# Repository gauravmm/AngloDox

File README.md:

# AngloDox Keyboard

This is yet another split keyboard with the following features:

- Per-key RGB LEDs
- Separate function row
- RC-circuit debouncing for each key (the internal pullups allow you to swap switches while the keyboard is on!)
- Kailh hot-swap sockets
- USB-C connectors (but I2C protocol!) for the halves, with ESD protection
- Key polling via shift register instead of matrix
- Entirely manufacturable by JLCPCB, using basic parts as much as possible.

### Keyboard Layout

The keyboard layout is specified in `keyboard-layout.json` and can be edited in [KLE](http://www.keyboard-layout-editor.com/). The current layout is based on the reference ANSI-104 layout, with a macro column on the left, a collapsed arrow cluster on the right, and added thumb clusters from the venerable Ergodox keyboard.

The current layout has 46 keys on the left and 54 on the right, for a total of 100 keys.

## Development

This relies on a combination of scripts and hand-routing. Here's the general workflow:

    1. Generate the basic circuitry as a hierarchical schematic in KiCad.
    2. Specify a key layout as a [http://www.keyboard-layout-editor.com/#/](KLE) JSON file.
    3. Run the [KLE Placement Plugin](TODO) for the key layout.
    4. Specify the layout for each key next to the schematic for the key.
    5. Enforce the layout using the [HierarchicalPCB plugin](https://github.com/gauravmm/HierarchicalPcb).
    6. Route the parts between keys, using the swap positions option in the KLE Placement Plugin to improve performance.

### Regenerate KiCad Library

The Kicad library is generated using [JLC2KiCad_lib](https://github.com/TousstNicolas/JLC2KiCad_lib). To regenerate the library, run:

```bash
JLC2KiCadLib C1525 C25779 C36871 C965555 \
    -dir temp_jlc_import/
```

Then merge the symbol and footprint libraries into the main library manually. Remember to update the Value field of the symbols.

When setting up the Footprint library, set the nickname to `footprint`.

### Design Notes

Component selection is driven by what is available on JLCPCB as a basic part, making construction as cheap as possible. The only extended parts are the USB ESD protection circuit and the RJ11 connectors.

#### Crystal Design

We choose a [generic 12MHz oscillator](https://jlcpcb.com/partdetail/YangxingTech-X322512MSB4SI/C9002) as it is the cheapest basic part available on LCSC. As the load capacitance is 20pF, and the stray capacitance is assumed to be 5pF, we need a pair of 30pF capacitors to get the right frequency. (See [section 3.3 of the application note](https://www.st.com/resource/en/application_note/cd00221665-oscillator-design-guide-for-stm8af-al-s-stm32-mcus-and-mpus-stmicroelectronics.pdf) for the derivation.)

#### ESD Protection

For peace of mind, we add ESD protection to both USB-C ports.

1. Use a [generic bi-directional 6V TVS diode](https://jlcpcb.com/partdetail/Liown-SMF60CA/C2990473) between `VBUS` and `GND`.
2. Use a [USB-specific ESD protection circuit](https://jlcpcb.com/partdetail/Stmicroelectronics-USBLC62SC6/C7519) on the data lines. This is one of the few extended parts we use. This is based on the suggestions in [Phil's Lab tutorial](https://youtu.be/C7-8nUU6e3E?t=3842).
3. Short shield pins to GND directly. (This disagrees with the tutorial mentioned above.)

#### Half-to-half Connection

The halves are connected via USB-C to USB-C cables. This is preferable to TRRS cables (which have a nasty habit of shorting connections) and RJ11 cables (which are painfully tall and would have to be hand-soldered later). Since we're already paying the extended part fee for the connector, we might as well use them and enjoy the reversible connection it grants us.

To prevent damage from accidental connections, we apply the same ESD protections to the half-to-half connections as we do to the legitimate USB-C port.

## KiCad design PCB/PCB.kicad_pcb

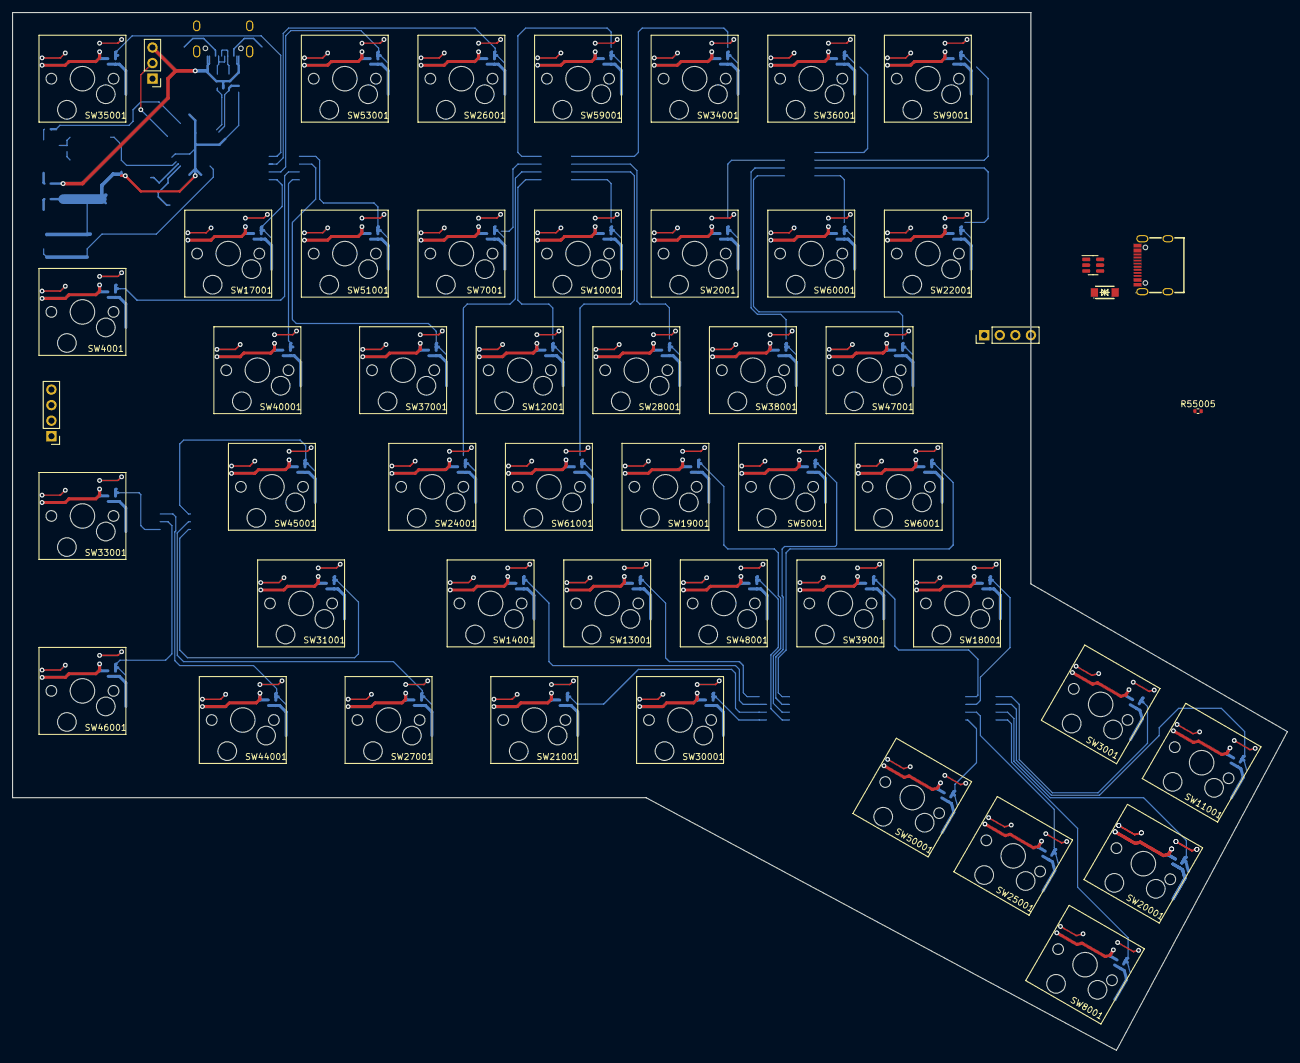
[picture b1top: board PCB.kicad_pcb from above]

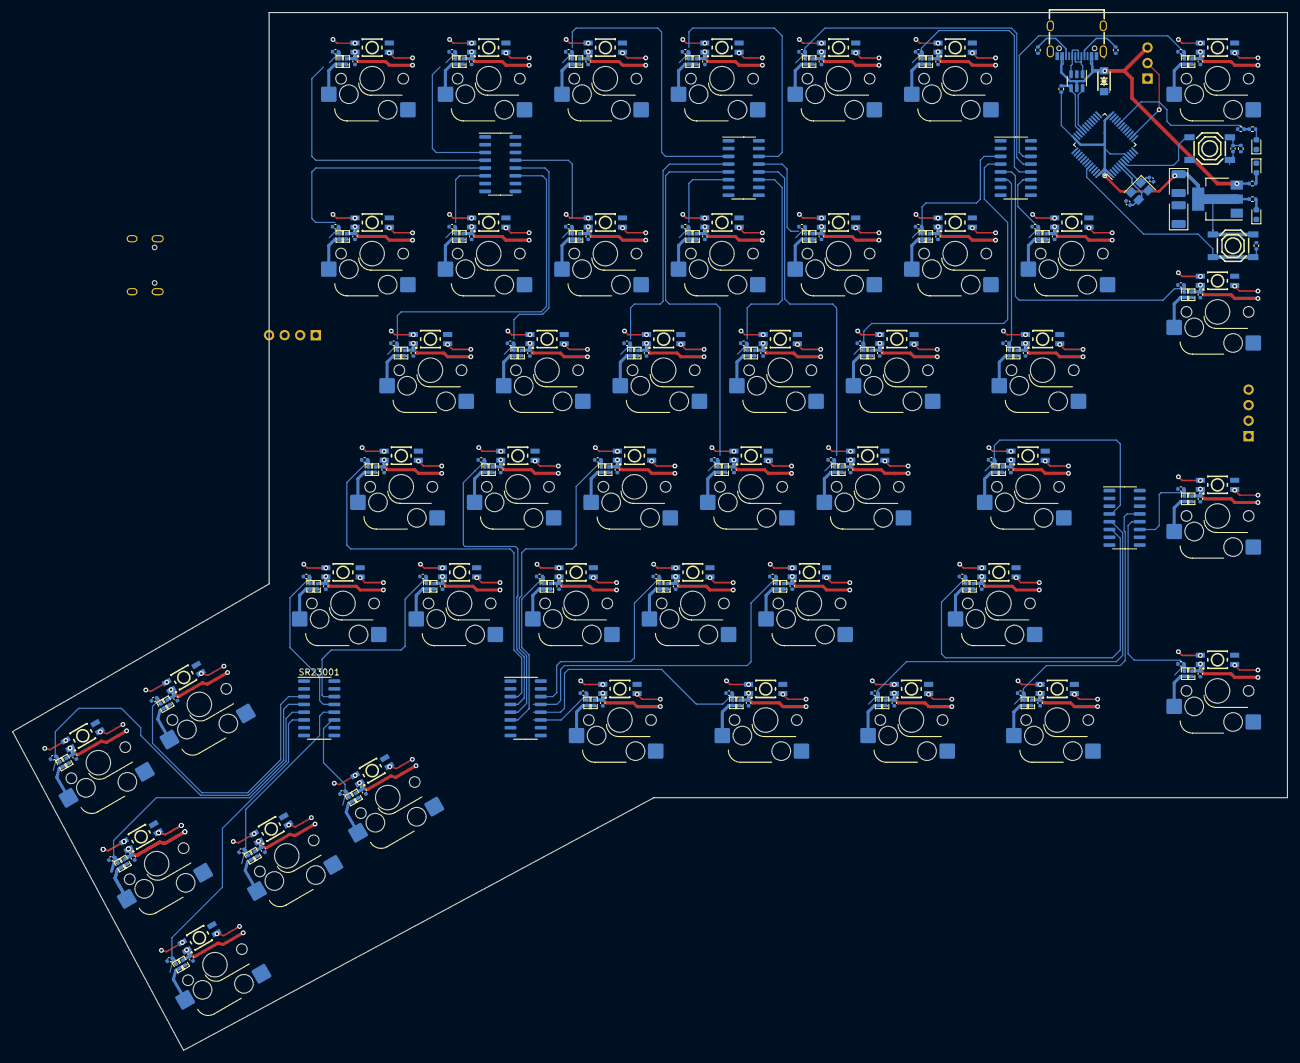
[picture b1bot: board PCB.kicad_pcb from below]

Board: 2 copper layers, 208.3 x 169.5 mm, 308 parts (256 on the bottom side), 129 nets.

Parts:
C55001, C55002: 30pF; C_0402_1005Metric
C55012: 100nF; C_0402_1005Metric
C55013, C55014: 100uF; CP_EIA-3528-15_AVX-H
CL2001, CL3001, CL4001, CL5001, CL6001, CL7001, CL8001, CL9001, CL10001, CL11001, CL12001, CL13001, CL14001, CL17001, CL18001, CL19001, CL20001, CL21001, CL22001, CL24001, CL25001, CL26001, CL27001, CL28001, CL30001, CL31001, CL33001, CL34001, CL35001, CL36001, CL37001, CL38001, CL39001, CL40001, CL44001, CL45001, CL46001, CL47001, CL48001, CL50001, CL51001, CL53001, CL59001, CL60001, CL61001: 100nF; C_0402_1005Metric
CS2001, CS3001, CS4001, CS5001, CS6001, CS7001, CS8001, CS9001, CS10001, CS11001, CS12001, CS13001, CS14001, CS17001, CS18001, CS19001, CS20001, CS21001, CS22001, CS24001, CS25001, CS26001, CS27001, CS28001, CS30001, CS31001, CS33001, CS34001, CS35001, CS36001, CS37001, CS38001, CS39001, CS40001, CS44001, CS45001, CS46001, CS47001, CS48001, CS50001, CS51001, CS53001, CS59001, CS60001, CS61001: 100nF; C_0402_1005Metric
D55001, D55003, D55004: Red; LED_0603_1608Metric
D55002, D60001: 6V ESD; SOD-123FL_L2.8-W1.8-LS3.7-BI
J55001: Debug; PinHeader_1x04_P2.54mm_Vertical
J60001: ALS; PinHeader_1x03_P2.54mm_Vertical
J60003: I2C; PinHeader_1x04_P2.54mm_Vertical
PB52001, PB55001: TS-1187A-B-A-B; SW-SMD_4P-L5.1-W5.1-P3.70-LS6.5-TL-2
R55001, R55003, R55004: 15k; R_0402_1005Metric
R55002, R55010: 1.5k; R_0402_1005Metric
R55005, R55006, R55007, R55008, R55009: 5.1k; R_0402_1005Metric
RA2001, RA3001, RA4001, RA5001, RA6001, RA7001, RA8001, RA9001, RA10001, RA11001, RA12001, RA13001, RA14001, RA17001, RA18001, RA19001, RA20001, RA21001, RA22001, RA24001, RA25001, RA26001, RA27001, RA28001, RA30001, RA31001, RA33001, RA34001, RA35001, RA36001, RA37001, RA38001, RA39001, RA40001, RA44001, RA45001, RA46001, RA47001, RA48001, RA50001, RA51001, RA53001, RA59001, RA60001, RA61001: 68kΩ; R0402
RB2001, RB3001, RB4001, RB5001, RB6001, RB7001, RB8001, RB9001, RB10001, RB11001, RB12001, RB13001, RB14001, RB17001, RB18001, RB19001, RB20001, RB21001, RB22001, RB24001, RB25001, RB26001, RB27001, RB28001, RB30001, RB31001, RB33001, RB34001, RB35001, RB36001, RB37001, RB38001, RB39001, RB40001, RB44001, RB45001, RB46001, RB47001, RB48001, RB50001, RB51001, RB53001, RB59001, RB60001, RB61001: 33kΩ; R0402
SR15001, SR16001, SR23001, SR32001, SR42001, SR54001: 74HC165; SOIC-16_3.9x9.9mm_P1.27mm
STM55001: STM32F103C8Tx; LQFP-48_7x7mm_P0.5mm
SW2001, SW3001, SW4001, SW5001, SW6001, SW7001, SW8001, SW9001, SW10001, SW11001, SW12001, SW13001, SW14001, SW17001, SW18001, SW19001, SW20001, SW21001, SW22001, SW24001, SW25001, SW26001, SW27001, SW28001, SW30001, SW31001, SW33001, SW34001, SW35001, SW36001, SW37001, SW38001, SW39001, SW40001, SW44001, SW45001, SW46001, SW47001, SW48001, SW50001, SW51001, SW53001, SW59001, SW60001, SW61001: SW_Push; SW_Hotswap_Kailh_MX
U2001, U3001, U4001, U5001, U6001, U7001, U8001, U9001, U10001, U11001, U12001, U13001, U14001, U17001, U18001, U19001, U20001, U21001, U22001, U24001, U25001, U26001, U27001, U28001, U30001, U31001, U33001, U34001, U35001, U36001, U37001, U38001, U39001, U40001, U44001, U45001, U46001, U47001, U48001, U50001, U51001, U53001, U59001, U60003, U61001: SK6812MINI-E_C5149201; LED-SMD_L3.2-W2.8-TR
U55001: AMS1117-3.3; SOT-223-3_TabPin2
U55002, U60001: TYPE-C-31-M-12; USB-C_SMD-TYPE-C-31-M-12
U55003, U60002: USBLC6-2SC6; SOT-23-6
X55001: Crystal; Crystal_SMD_3225-4Pin_3.2x2.5mm

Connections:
+3.3V: C55014.1, J55001.1, PB55001.1 (A), PB55001.2 (B), R55004.1, R55007.1, R55010.1, STM55001.1 (VBAT), STM55001.9 (VDDA), STM55001.24 (VDD), STM55001.36 (VDD), STM55001.48 (VDD), U55001.2 (VO)
+5V: C55013.1, CL2001.2, CL3001.2, CL4001.2, CL5001.2, CL6001.2, CL7001.2, CL8001.2, CL9001.2, CL10001.2, CL11001.2, CL12001.2, CL13001.2, CL14001.2, CL17001.2, CL18001.2, CL19001.2, CL20001.2, CL21001.2, CL22001.2, CL24001.2, CL25001.2, CL26001.2, CL27001.2, CL28001.2, CL30001.2, CL31001.2, CL33001.2, CL34001.2, CL35001.2, CL36001.2, CL37001.2, CL38001.2, CL39001.2, CL40001.2, CL44001.2, CL45001.2, CL46001.2, CL47001.2, CL48001.2, CL50001.2, CL51001.2, CL53001.2, CL59001.2, CL60001.2, CL61001.2, D55002.2, D60001.2, J60001.3, J60003.1, R55005.1, RA2001.2, RA3001.2, RA4001.2, RA5001.2, RA6001.2, RA7001.2, RA8001.2, RA9001.2, RA10001.2, RA11001.2, RA12001.2, RA13001.2, RA14001.2, RA17001.2, RA18001.2, RA19001.2, RA20001.2, RA21001.2, RA22001.2, RA24001.2, RA25001.2, RA26001.2, RA27001.2, RA28001.2, RA30001.2, RA31001.2, RA33001.2, RA34001.2, RA35001.2, RA36001.2, RA37001.2, RA38001.2, RA39001.2, RA40001.2, RA44001.2, RA45001.2, RA46001.2, RA47001.2, RA48001.2, RA50001.2, RA51001.2, RA53001.2, RA59001.2, RA60001.2, RA61001.2, SR15001.16 (VCC), SR16001.16 (VCC), SR23001.16 (VCC), SR32001.16 (VCC), SR42001.16 (VCC), SR54001.16 (VCC), U2001.1 (VDD), U3001.1 (VDD), U4001.1 (VDD), U5001.1 (VDD), U6001.1 (VDD), U7001.1 (VDD), U8001.1 (VDD), U9001.1 (VDD), U10001.1 (VDD), U11001.1 (VDD), U12001.1 (VDD), U13001.1 (VDD), U14001.1 (VDD), U17001.1 (VDD), U18001.1 (VDD), U19001.1 (VDD), U20001.1 (VDD), U21001.1 (VDD), U22001.1 (VDD), U24001.1 (VDD), U25001.1 (VDD), U26001.1 (VDD), U27001.1 (VDD), U28001.1 (VDD), U30001.1 (VDD), U31001.1 (VDD), U33001.1 (VDD), U34001.1 (VDD), U35001.1 (VDD), U36001.1 (VDD), U37001.1 (VDD), U38001.1 (VDD), U39001.1 (VDD), U40001.1 (VDD), U44001.1 (VDD), U45001.1 (VDD), U46001.1 (VDD), U47001.1 (VDD), U48001.1 (VDD), U50001.1 (VDD), U51001.1 (VDD), U53001.1 (VDD), U55001.3 (VI), U55002.A4 (VBUS), U55002.A9 (VBUS), U55002.B4 (VBUS), U55002.B9 (VBUS), U55003.5 (VBUS), U59001.1 (VDD), U60001.A4 (VBUS), U60001.A9 (VBUS), U60001.B4 (VBUS), U60001.B9 (VBUS), U60002.5 (VBUS), U60003.1 (VDD), U61001.1 (VDD)
/Left Half/8-Key Module1/SR_OUT: SR15001.10 (DS), SR42001.9 (Q7)
/Left Half/8-Key Module2/SR_OUT: SR15001.9 (Q7), SR16001.10 (DS)
/Left Half/8-Key Module3/SR_OUT: SR16001.9 (Q7), SR32001.10 (DS)
/Left Half/8-Key Module4/SR_OUT: SR23001.10 (DS), SR32001.9 (Q7)
/Left Half/8-Key Module5/SR_OUT: SR23001.9 (Q7), STM55001.38 (PA15)
/Left Half/8-Key Module/SR_CLOCK: SR15001.2 (CP), SR16001.2 (CP), SR23001.2 (CP), SR32001.2 (CP), SR42001.2 (CP), SR54001.2 (CP), STM55001.12 (PA2)
/Left Half/8-Key Module/SR_LOAD: SR15001.1 (~PL), SR16001.1 (~PL), SR23001.1 (~PL), SR32001.1 (~PL), SR42001.1 (~PL), SR54001.1 (~PL), STM55001.11 (PA1)
/Left Half/8-Key Module/SR_OUT: SR42001.10 (DS), SR54001.9 (Q7)
/Left Half/HALF_CONN_C: U60001.A5 (CC1), U60001.B5 (CC2)
/Left Half/HALF_CONN_N: U60001.A7 (DN1), U60001.B7 (DN2), U60002.1 (I/O1)
/Left Half/HALF_CONN_P: U60001.A6 (DP1), U60001.B6 (DP2), U60002.3 (I/O2)
/Left Half/HALF_CONN_S: U60001.A8 (SBU1), U60001.B8 (SBU2)
/Left Half/HALF_SCL: STM55001.42 (PB6), U60002.4 (I/O2)
/Left Half/HALF_SDA: STM55001.43 (PB7), U60002.6 (I/O1)
/Left Half/Key Unit0/SwitchOutput: CS9001.2, RB9001.1
/Left Half/Key Unit1/SwitchOutput: CS5001.2, RB5001.1, SR32001.4 (D5)
/Left Half/Key Unit2/SwitchOutput: CS8001.2, RB8001.1, SR23001.6 (D7)
/Left Half/Key Unit3/SwitchOutput: CS4001.2, RB4001.1, SR15001.5 (D6)
/Left Half/Key Unit4/SwitchOutput: CS7001.2, RB7001.1
/Left Half/Key Unit5/SwitchOutput: CS6001.2, RB6001.1, SR32001.3 (D4)
/Left Half/Key Unit6/SwitchOutput: CS2001.2, RB2001.1
/Left Half/Key Unit7/SwitchOutput: CS3001.2, RB3001.1, SR23001.3 (D4)
/Left Half/Key Unit11/SwitchOutput: CS18001.2, RB18001.1, SR23001.13 (D2)
/Left Half/Key Unit14/SwitchOutput: CS14001.2, RB14001.1, SR32001.13 (D2)
/Left Half/Key Unit15/SwitchOutput: CS17001.2, RB17001.1, SR15001.11 (D0)
/Left Half/Key Unit16/SwitchOutput: CS10001.2, RB10001.1
/Left Half/Key Unit17/SwitchOutput: CS19001.2, RB19001.1, SR32001.5 (D6)
/Left Half/Key Unit18/SwitchOutput: CS13001.2, RB13001.1, SR32001.14 (D3)
/Left Half/Key Unit19/SwitchOutput: CS12001.2, RB12001.1
/Left Half/Key Unit20/SwitchOutput: CS11001.2, RB11001.1, SR23001.4 (D5)
/Left Half/Key Unit21/SwitchOutput: CS26001.2, RB26001.1, SR15001.13 (D2)
/Left Half/Key Unit22/SwitchOutput: CS22001.2, RB22001.1
/Left Half/Key Unit23/SwitchOutput: CS21001.2, RB21001.1, SR32001.12 (D1)
/Left Half/Key Unit24/SwitchOutput: CS20001.2, RB20001.1, SR23001.5 (D6)
/Left Half/Key Unit25/SwitchOutput: CS24001.2, RB24001.1
/Left Half/Key Unit26/SwitchOutput: CS27001.2, RB27001.1, SR54001.5 (D6)
/Left Half/Key Unit27/SwitchOutput: CS25001.2, RB25001.1, SR23001.12 (D1)
/Left Half/Key Unit28/SwitchOutput: CS28001.2, RB28001.1
/Left Half/Key Unit29/SwitchOutput: CS36001.2, RB36001.1
/Left Half/Key Unit30/SwitchOutput: CS30001.2, RB30001.1, SR32001.11 (D0)
/Left Half/Key Unit31/SwitchOutput: CS35001.2, RB35001.1, SR15001.14 (D3)
/Left Half/Key Unit32/SwitchOutput: CS37001.2, RB37001.1, SR15001.4 (D5)
/Left Half/Key Unit33/SwitchOutput: CS33001.2, RB33001.1, SR54001.11 (D0)
/Left Half/Key Unit34/SwitchOutput: CS31001.2, RB31001.1, SR54001.6 (D7)
/Left Half/Key Unit35/SwitchOutput: CS34001.2, RB34001.1
/Left Half/Key Unit36/SwitchOutput: CS38001.2, RB38001.1
/Left Half/Key Unit37/SwitchOutput: CS39001.2, RB39001.1, SR23001.14 (D3)
/Left Half/Key Unit38/SwitchOutput: CS46001.2, RB46001.1, SR54001.12 (D1)
/Left Half/Key Unit39/SwitchOutput: CS47001.2, RB47001.1
/Left Half/Key Unit40/SwitchOutput: CS50001.2, RB50001.1, SR23001.11 (D0)
/Left Half/Key Unit41/SwitchOutput: CS48001.2, RB48001.1, SR32001.6 (D7)
/Left Half/Key Unit42/SwitchOutput: CS40001.2, RB40001.1, SR15001.6 (D7)
/Left Half/Key Unit43/SwitchOutput: CS44001.2, RB44001.1, SR54001.13 (D2)
/Left Half/Key Unit44/SwitchOutput: CS45001.2, RB45001.1, SR54001.4 (D5)
/Left Half/Key Unit45/SwitchOutput: CS53001.2, RB53001.1, SR15001.12 (D1)
/Left Half/Key Unit47/SwitchOutput: CS51001.2, RB51001.1, SR15001.3 (D4)
/Left Half/Key Unit49/SwitchOutput: CS60001.2, RB60001.1
/Left Half/Key Unit50/SwitchOutput: CS61001.2, RB61001.1
/Left Half/Key Unit51/SwitchOutput: CS59001.2, RB59001.1
/Left Half/STM32 Module/ADC12_IN4: J60001.2, STM55001.14 (PA4)
/Left Half/STM32 Module/BOOT0: PB55001.3 (C), PB55001.4 (D), R55003.1, STM55001.44 (BOOT0)
/Left Half/STM32 Module/BOOT1: R55001.1, R55002.1, STM55001.20 (PB2)
/Left Half/STM32 Module/I2C2_SCL: J60003.3, STM55001.21 (PB10)
/Left Half/STM32 Module/I2C2_SDA: J60003.2, STM55001.22 (PB11)
/Left Half/STM32 Module/NRST: PB52001.4 (D), STM55001.7 (NRST)
/Left Half/STM32 Module/USBDN: STM55001.32 (PA11), U55003.6 (I/O1)
/Left Half/STM32 Module/USBDP: R55010.2, STM55001.33 (PA12), U55003.4 (I/O2)
/Left Half/STM32 Module/USB_DN: U55002.A7 (DN1), U55002.B7 (DN2), U55003.1 (I/O1)
/Left Half/STM32 Module/USB_DP: U55002.A6 (DP1), U55002.B6 (DP2), U55003.3 (I/O2)
GND: C55001.1, C55002.1, C55013.2, C55014.2, CL2001.1, CL3001.1, CL4001.1, CL5001.1, CL6001.1, CL7001.1, CL8001.1, CL9001.1, CL10001.1, CL11001.1, CL12001.1, CL13001.1, CL14001.1, CL17001.1, CL18001.1, CL19001.1, CL20001.1, CL21001.1, CL22001.1, CL24001.1, CL25001.1, CL26001.1, CL27001.1, CL28001.1, CL30001.1, CL31001.1, CL33001.1, CL34001.1, CL35001.1, CL36001.1, CL37001.1, CL38001.1, CL39001.1, CL40001.1, CL44001.1, CL45001.1, CL46001.1, CL47001.1, CL48001.1, CL50001.1, CL51001.1, CL53001.1, CL59001.1, CL60001.1, CL61001.1, CS2001.1, CS3001.1, CS4001.1, CS5001.1, CS6001.1, CS7001.1, CS8001.1, CS9001.1, CS10001.1, CS11001.1, CS12001.1, CS13001.1, CS14001.1, CS17001.1, CS18001.1, CS19001.1, CS20001.1, CS21001.1, CS22001.1, CS24001.1, CS25001.1, CS26001.1, CS27001.1, CS28001.1, CS30001.1, CS31001.1, CS33001.1, CS34001.1, CS35001.1, CS36001.1, CS37001.1, CS38001.1, CS39001.1, CS40001.1, CS44001.1, CS45001.1, CS46001.1, CS47001.1, CS48001.1, CS50001.1, CS51001.1, CS53001.1, CS59001.1, CS60001.1, CS61001.1, D55001.1 (K), D55002.1, D55003.1 (K), D55004.1 (K), D60001.1, J55001.4, J60001.1, J60003.4, PB52001.2 (B), R55001.2, R55003.2, R55008.1, R55009.1, SR15001.8 (GND), SR16001.8 (GND), SR23001.8 (GND), SR32001.8 (GND), SR42001.8 (GND), SR54001.8 (GND), STM55001.8 (VSSA), STM55001.23 (VSS), STM55001.35 (VSS), STM55001.47 (VSS), SW2001.2, SW3001.2, SW4001.2, SW5001.2, SW6001.2, SW7001.2, SW8001.2, SW9001.2, SW10001.2, SW11001.2, SW12001.2, SW13001.2, SW14001.2, SW17001.2, SW18001.2, SW19001.2, SW20001.2, SW21001.2, SW22001.2, SW24001.2, SW25001.2, SW26001.2, SW27001.2, SW28001.2, SW30001.2, SW31001.2, SW33001.2, SW34001.2, SW35001.2, SW36001.2, SW37001.2, SW38001.2, SW39001.2, SW40001.2, SW44001.2, SW45001.2, SW46001.2, SW47001.2, SW48001.2, SW50001.2, SW51001.2, SW53001.2, SW59001.2, SW60001.2, SW61001.2, U2001.3 (GND), U3001.3 (GND), U4001.3 (GND), U5001.3 (GND), U6001.3 (GND), U7001.3 (GND), U8001.3 (GND), U9001.3 (GND), U10001.3 (GND), U11001.3 (GND), U12001.3 (GND), U13001.3 (GND), U14001.3 (GND), U17001.3 (GND), U18001.3 (GND), U19001.3 (GND), U20001.3 (GND), U21001.3 (GND), U22001.3 (GND), U24001.3 (GND), U25001.3 (GND), U26001.3 (GND), U27001.3 (GND), U28001.3 (GND), U30001.3 (GND), U31001.3 (GND), U33001.3 (GND), U34001.3 (GND), U35001.3 (GND), U36001.3 (GND), U37001.3 (GND), U38001.3 (GND), U39001.3 (GND), U40001.3 (GND), U44001.3 (GND), U45001.3 (GND), U46001.3 (GND), U47001.3 (GND), U48001.3 (GND), U50001.3 (GND), U51001.3 (GND), U53001.3 (GND), U55001.1 (GND), U55002.0 (SH), U55002.A1 (GND), U55002.A12 (GND), U55002.B1 (GND), U55002.B12 (GND), U55003.2 (GND), U59001.3 (GND), U60001.0 (SH), U60001.A1 (GND), U60001.A12 (GND), U60001.B1 (GND), U60001.B12 (GND), U60002.2 (GND), U60003.3 (GND), U61001.3 (GND), X55001.2, X55001.4
unnamed: D55001.2 (A), R55002.2
unnamed: D55003.2 (A), R55006.2
unnamed: D55004.2 (A), R55007.2
unnamed: J55001.2, STM55001.34 (PA13)
unnamed: J55001.3, STM55001.37 (PA14)
unnamed: C55012.1, PB52001.1 (A)
unnamed: C55012.2, PB52001.3 (C), R55004.2
unnamed: R55005.2, R55006.1
unnamed: RA2001.1, RB2001.2, SW2001.1
unnamed: RA3001.1, RB3001.2, SW3001.1
unnamed: RA4001.1, RB4001.2, SW4001.1
unnamed: RA5001.1, RB5001.2, SW5001.1
unnamed: RA6001.1, RB6001.2, SW6001.1
unnamed: RA7001.1, RB7001.2, SW7001.1
unnamed: RA8001.1, RB8001.2, SW8001.1
unnamed: RA9001.1, RB9001.2, SW9001.1
unnamed: RA10001.1, RB10001.2, SW10001.1
unnamed: RA11001.1, RB11001.2, SW11001.1
unnamed: RA12001.1, RB12001.2, SW12001.1
unnamed: RA13001.1, RB13001.2, SW13001.1
unnamed: RA14001.1, RB14001.2, SW14001.1
unnamed: RA17001.1, RB17001.2, SW17001.1
unnamed: RA18001.1, RB18001.2, SW18001.1
unnamed: RA19001.1, RB19001.2, SW19001.1
unnamed: RA20001.1, RB20001.2, SW20001.1
unnamed: RA21001.1, RB21001.2, SW21001.1
unnamed: RA22001.1, RB22001.2, SW22001.1
unnamed: RA24001.1, RB24001.2, SW24001.1
unnamed: RA25001.1, RB25001.2, SW25001.1
unnamed: RA26001.1, RB26001.2, SW26001.1
unnamed: RA27001.1, RB27001.2, SW27001.1
unnamed: RA28001.1, RB28001.2, SW28001.1
unnamed: RA30001.1, RB30001.2, SW30001.1
unnamed: RA31001.1, RB31001.2, SW31001.1
unnamed: RA33001.1, RB33001.2, SW33001.1
unnamed: RA34001.1, RB34001.2, SW34001.1
unnamed: RA35001.1, RB35001.2, SW35001.1
unnamed: RA36001.1, RB36001.2, SW36001.1
unnamed: RA37001.1, RB37001.2, SW37001.1
unnamed: RA38001.1, RB38001.2, SW38001.1
unnamed: RA39001.1, RB39001.2, SW39001.1
unnamed: RA40001.1, RB40001.2, SW40001.1
unnamed: RA44001.1, RB44001.2, SW44001.1
unnamed: RA45001.1, RB45001.2, SW45001.1
unnamed: RA46001.1, RB46001.2, SW46001.1
unnamed: RA47001.1, RB47001.2, SW47001.1
unnamed: RA48001.1, RB48001.2, SW48001.1
unnamed: RA50001.1, RB50001.2, SW50001.1
unnamed: RA51001.1, RB51001.2, SW51001.1
unnamed: RA53001.1, RB53001.2, SW53001.1
unnamed: RA59001.1, RB59001.2, SW59001.1
unnamed: RA60001.1, RB60001.2, SW60001.1
unnamed: RA61001.1, RB61001.2, SW61001.1
unnamed: C55001.2, STM55001.5 (PD0), X55001.3
unnamed: C55002.2, STM55001.6 (PD1), X55001.1
unnamed: R55008.2, U55002.A5 (CC1)
unnamed: R55009.2, U55002.B5 (CC2)

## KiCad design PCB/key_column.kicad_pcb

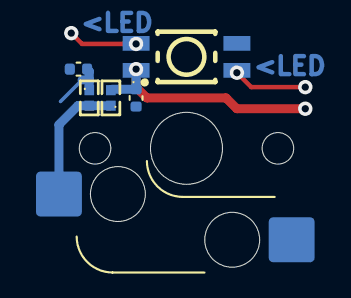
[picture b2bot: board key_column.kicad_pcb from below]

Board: 2 copper layers, 6 parts (5 on the bottom side), 4 nets.

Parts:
CL1201: 100nF; C_0402_1005Metric
CS1201: 100nF; C_0402_1005Metric
RA1201: 68kΩ; R0402
RB1201: 33kΩ; R0402
SW1201: SW_Push; SW_Hotswap_Kailh_MX
U1201: SK6812MINI-E_C5149201; LED-SMD_L3.2-W2.8-TR

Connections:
+5V: CL1201.2, RA1201.2, U1201.1 (VDD)
/SwitchOutput: CS1201.2, RB1201.1
GND: CL1201.1, CS1201.1, SW1201.2, U1201.3 (GND)
unnamed: RA1201.1, RB1201.2, SW1201.1

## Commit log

2023-07-26 PCB started.
2023-07-27 Figured out the layout, now working on the PCB for each half.
2023-07-27 Moved some modifier keys to the thumb cluster.
2023-07-29 Working on STM32 circuit
2023-07-29 Removed stm32, we're using a BluePill instead.
2023-07-29 Done with STM32
2023-07-29 Ready to work on PCB
2023-08-12 Plugin works.
2023-08-20 Laying out the PCB.
2023-08-20 Removed 8-key units, now using the PCB view to handle routing the keys to the SOIP shift registers.
2024-03-04 Updated schematics for KiCAD 8
